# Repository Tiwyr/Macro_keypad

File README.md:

# Custom Macro Keypad

A custom-built programmable macro keypad featuring 12 mechanical keys, three rotary encoders, a dedicated layer button, and a color display.

The keypad is powered by an Adafruit KB2040 running CircuitPython and KMK firmware. It currently supports up to four configurable layers, allowing each key and encoder direction to perform a different action on every layer.

## Features

- 12 individually programmable mechanical keys
- Three programmable rotary encoders
- Dedicated layer-selection button
- Support for up to four configuration layers
- 320 × 240 color display
- Keyboard, media-key, macro, URL, application-launching, and MIDI actions
- Custom PCB
- Custom 3D-printable enclosure and keycaps
- Configurable display icons and layer names
- CircuitPython and KMK-based firmware

## Personal configuration

I currently use the three rotary encoders to control separate audio channels in SteelSeries GG Sonar. This is why the encoder logos on the chassit panel are what they are.

The encoder actions are programmable, and the encoder panel design can be modified using the included STEP or Fusion 360 files.

## Project structure

```text
Macro_keypad/
├── Board_Code/              CircuitPython and KMK firmware
├── Cad/                     Enclosure, keycap, and component models
├── Desktop_App/             Desktop configuration app in development
├── Macro_Keyboard_Circuit/  KiCad schematic and PCB files
└── images/                  README photographs and renders
```

## Firmware configuration

OBS! The config file is automatically configured using the desktop app.

Key and encoder actions are configured in:

```text
Board_Code/active_config.py
```

A basic key assignment looks like this:

```python
"KC.A"
```

Modifier combinations can be written directly:

```python
"KC.LCTRL(KC.C)"
"KC.LCTRL(KC.LSHIFT(KC.S))"
```

Other supported actions include:

```python
"KC.VOLU"
"KC.VOLD"
"URL:https://www.youtube.com/"
"LAUNCH:C:/Program Files/KiCad/10.0/bin/kicad.exe"
```

Each layer contains 12 key assignments. The three encoders have separate assignments for counterclockwise rotation, clockwise rotation, and their push-button action where applicable.

### Using the `MACRO:` wrapper

Use the `MACRO:` wrapper when one button should perform several actions, type text, include a delay, or behave differently when pressed, held, and released. Separate each part of a macro with `|`.

The supported macro commands are:

- `TEXT:` types text.
- `TAP:` presses and immediately releases a key or shortcut.
- `PRESS:` holds a key down.
- `RELEASE:` releases a held key.
- `DELAY:` waits for the specified number of milliseconds.

For example, this macro copies, waits 100 milliseconds, and then pastes:

```python
"MACRO:TAP:KC.LCTRL(KC.C)|DELAY:100|TAP:KC.LCTRL(KC.V)"
```

A key action without an explicit event prefix runs when the button is pressed i.e. `ON_PRESS:`. The optional event prefixes are:

- `ON_PRESS:` runs when the button is pressed.
- `ON_HOLD:` runs while the button is held.
- `ON_RELEASE:` runs when the button is released.

For example:

```python
"MACRO:ON_PRESS:TEXT:start|ON_HOLD:TAP:KC.A|ON_HOLD:DELAY:100|ON_RELEASE:TEXT:end"
```

Simple shortcuts do not require the macro wrapper and can be assigned directly, as shown above.

## Display icons

Icons are stored by layer and key number inside:

```text
Board_Code/images/
```

The desktop app has the feature to prepare images for the keypad display.

## CAD files

The `Cad` directory contains editable and printable files for the enclosure and keycaps, including:

- Fusion 360 files
- STEP models
- STL files
- 3MF print files
- Component reference models

The encoder logos can be edited to create a personalized panel.

## Desktop application

A PySide6 desktop application is currently in development.

The planned application will provide a graphical interface for:

- Editing key and encoder assignments
- Creating and managing profiles
- Changing layer names and display icons
- Sending configurations to the keypad
- Executing Windows-specific actions that cannot run directly on the board

At the moment, configuration is performed by editing `active_config.py` manually.

## Hardware

- Adafruit KB2040 with RP2040
- 12 mechanical keyboard switches
- Three rotary encoders
- ST7789-based 320 × 240 LCD
- Custom-designed PCB
- 3D-printed enclosure and keycaps

The gerber files for the PCB is found under `Macro_Keyboard_Cicuit`, for manufacturing I used [JLCPCB.com](https://jlcpcb.com/?from=VGEEEPCB1&utm_source=google&utm_medium=cpc&utm_campaign=23630608026&utm_content=803328468424&utm_term=p_pcb%20manufacturing&adgroupid=194779815580&utm_network=g_&gad_source=1&gad_campaignid=23630608026&gbraid=0AAAAApXmXsdJ7AZJWkuDSiIHlBB-qUlTP&gclid=CjwKCAjwvsvTBhBaEiwAmf-3njncny4jFNF5munrN3aUFo6y1D-hInMBf39UMtHOZ52Y8qgtHUBPVxoC710QAvD_BwE). Since the PCB is only two sided it is possible to manufacture by yourself if you have acess to the equipment. 

## Project status

This project is under active development. The keypad firmware, PCB, enclosure, display, keys, and encoders are functional. The desktop configuration application is still being developed.

## License

No license has been selected yet.

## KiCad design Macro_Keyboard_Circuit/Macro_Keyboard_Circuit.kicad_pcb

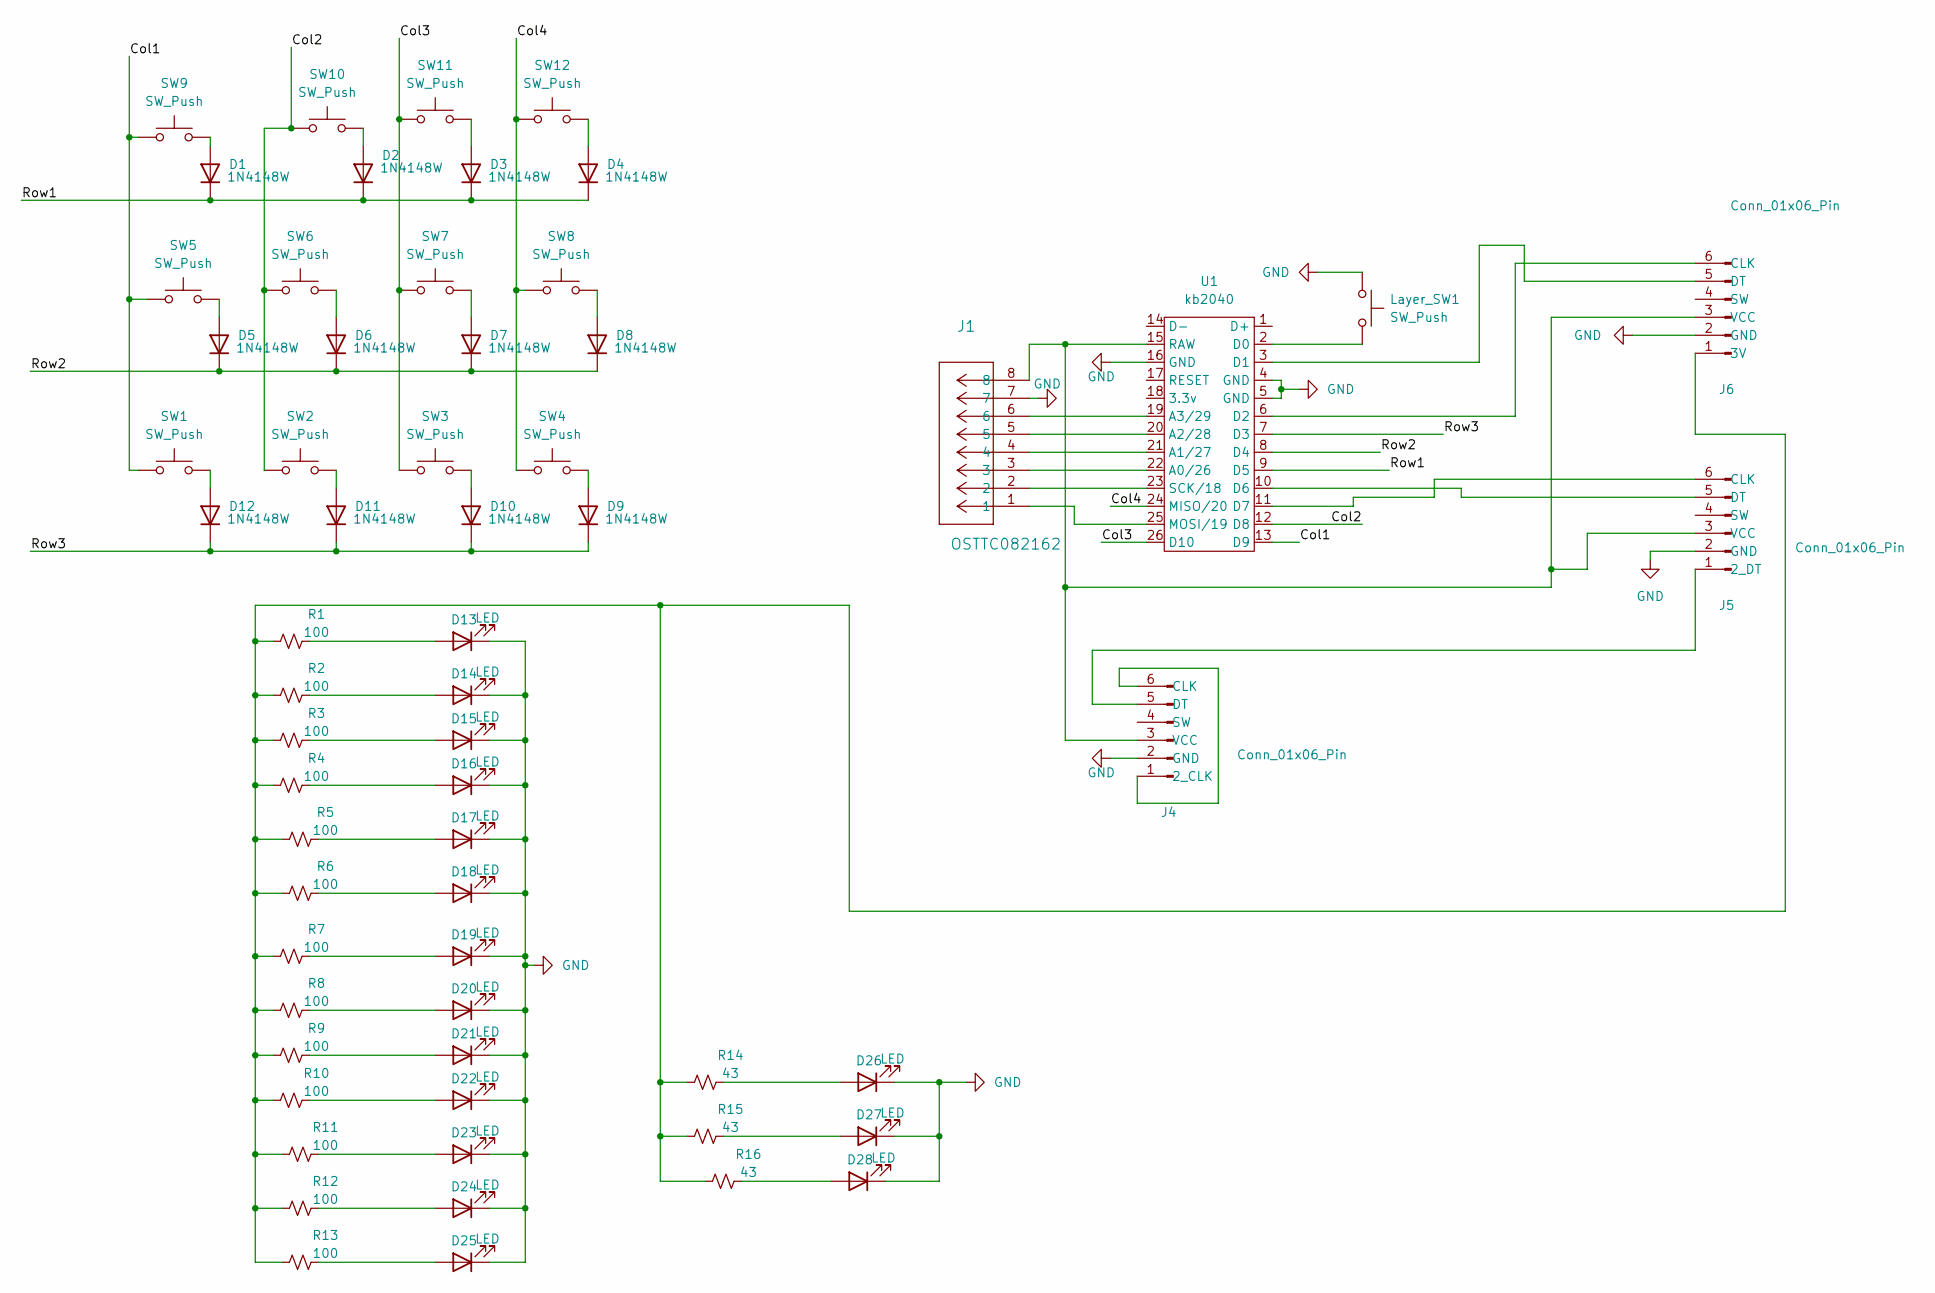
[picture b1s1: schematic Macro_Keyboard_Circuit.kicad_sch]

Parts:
D1, D2, D3, D4, D5, D6, D7, D8, D9, D10, D11, D12: 1N4148W; D_SOD-123
D13, D14, D15, D16, D17, D18, D19, D20, D21, D22, D23, D24, D25: LED; D_0603_1608Metric_Pad1.05x0.95mm_HandSolder_cherrymx_silk
D26, D27, D28: LED; D_A-405_P2.54mm_Vertical_AnodeUp
J1: OSTTC082162; CONN8_OSTTC082162_SHT
J4, J5, J6: Conn_01x06_Pin; PinHeader_1x06_P2.54mm_Vertical
Layer_SW1: SW_Push; SW_Cherry_modified
R1, R2, R3, R4, R5, R6, R7, R8, R9, R10, R11, R12, R13: 100; R_0603_1608Metric
R14, R15, R16: 43; R_0603_1608Metric
SW1, SW2, SW3, SW4, SW5, SW6, SW7, SW8, SW9, SW10, SW11, SW12: SW_Push; SW_Cherry_modified
U1: kb2040

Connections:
/Col1: SW1.1, SW5.1, SW9.1, U1.13 (D9)
/Col2: SW2.1, SW6.1, SW10.1, U1.12 (D8)
/Col3: SW3.1, SW7.1, SW11.1, U1.26 (D10)
/Col4: SW4.1, SW8.1, SW12.1, U1.24 (MISO/20)
/Row1: D1.1 (K), D2.1 (K), D3.1 (K), D4.1 (K), U1.9 (D5)
/Row2: D5.1 (K), D6.1 (K), D7.1 (K), D8.1 (K), U1.8 (D4)
/Row3: D9.1 (K), D10.1 (K), D11.1 (K), D12.1 (K), U1.7 (D3)
GND: D13.1 (K), D14.1 (K), D15.1 (K), D16.1 (K), D17.1 (K), D18.1 (K), D19.1 (K), D20.1 (K), D21.1 (K), D22.1 (K), D23.1 (K), D24.1 (K), D25.1 (K), D26.1 (K), D27.1 (K), D28.1 (K), J1.7, J4.2 (GND), J5.2 (GND), J6.2 (GND), Layer_SW1.1, U1.4 (GND), U1.5 (GND), U1.16 (GND)
unnamed: D1.2 (A), SW9.2
unnamed: D2.2 (A), SW10.2
unnamed: D3.2 (A), SW11.2
unnamed: D4.2 (A), SW12.2
unnamed: D5.2 (A), SW5.2
unnamed: D6.2 (A), SW6.2
unnamed: D7.2 (A), SW7.2
unnamed: D8.2 (A), SW8.2
unnamed: D9.2 (A), SW4.2
unnamed: D10.2 (A), SW3.2
unnamed: D11.2 (A), SW2.2
unnamed: D12.2 (A), SW1.2
unnamed: D13.2 (A), R1.2
unnamed: D14.2 (A), R2.2
unnamed: D15.2 (A), R3.2
unnamed: D16.2 (A), R4.2
unnamed: D17.2 (A), R5.2
unnamed: D18.2 (A), R6.2
unnamed: D19.2 (A), R7.2
unnamed: D20.2 (A), R8.2
unnamed: D21.2 (A), R9.2
unnamed: D22.2 (A), R10.2
unnamed: D23.2 (A), R11.2
unnamed: D24.2 (A), R12.2
unnamed: D25.2 (A), R13.2
unnamed: D26.2 (A), R14.2
unnamed: D27.2 (A), R15.2
unnamed: D28.2 (A), R16.2
unnamed: J4.1 (2_CLK), J4.6 (CLK)
unnamed: J4.5 (DT), J5.1 (2_DT)
unnamed: J1.8, J4.3 (VCC), J5.3 (VCC), J6.3 (VCC), U1.15 (RAW)
unnamed: J5.6 (CLK), U1.11 (D7)
unnamed: J5.5 (DT), U1.10 (D6)
unnamed: J6.1 (3V), R1.1, R2.1, R3.1, R4.1, R5.1, R6.1, R7.1, R8.1, R9.1, R10.1, R11.1, R12.1, R13.1, R14.1, R15.1, R16.1
unnamed: J6.6 (CLK), U1.6 (D2)
unnamed: J6.5 (DT), U1.3 (D1)
unnamed: J1.3, U1.22 (A0/26)
unnamed: J1.4, U1.21 (A1/27)
unnamed: J1.5, U1.20 (A2/28)
unnamed: J1.6, U1.19 (A3/29)
unnamed: Layer_SW1.2, U1.2 (D0)
unnamed: J1.1, U1.25 (MOSI/19)
unnamed: J1.2, U1.23 (SCK/18)

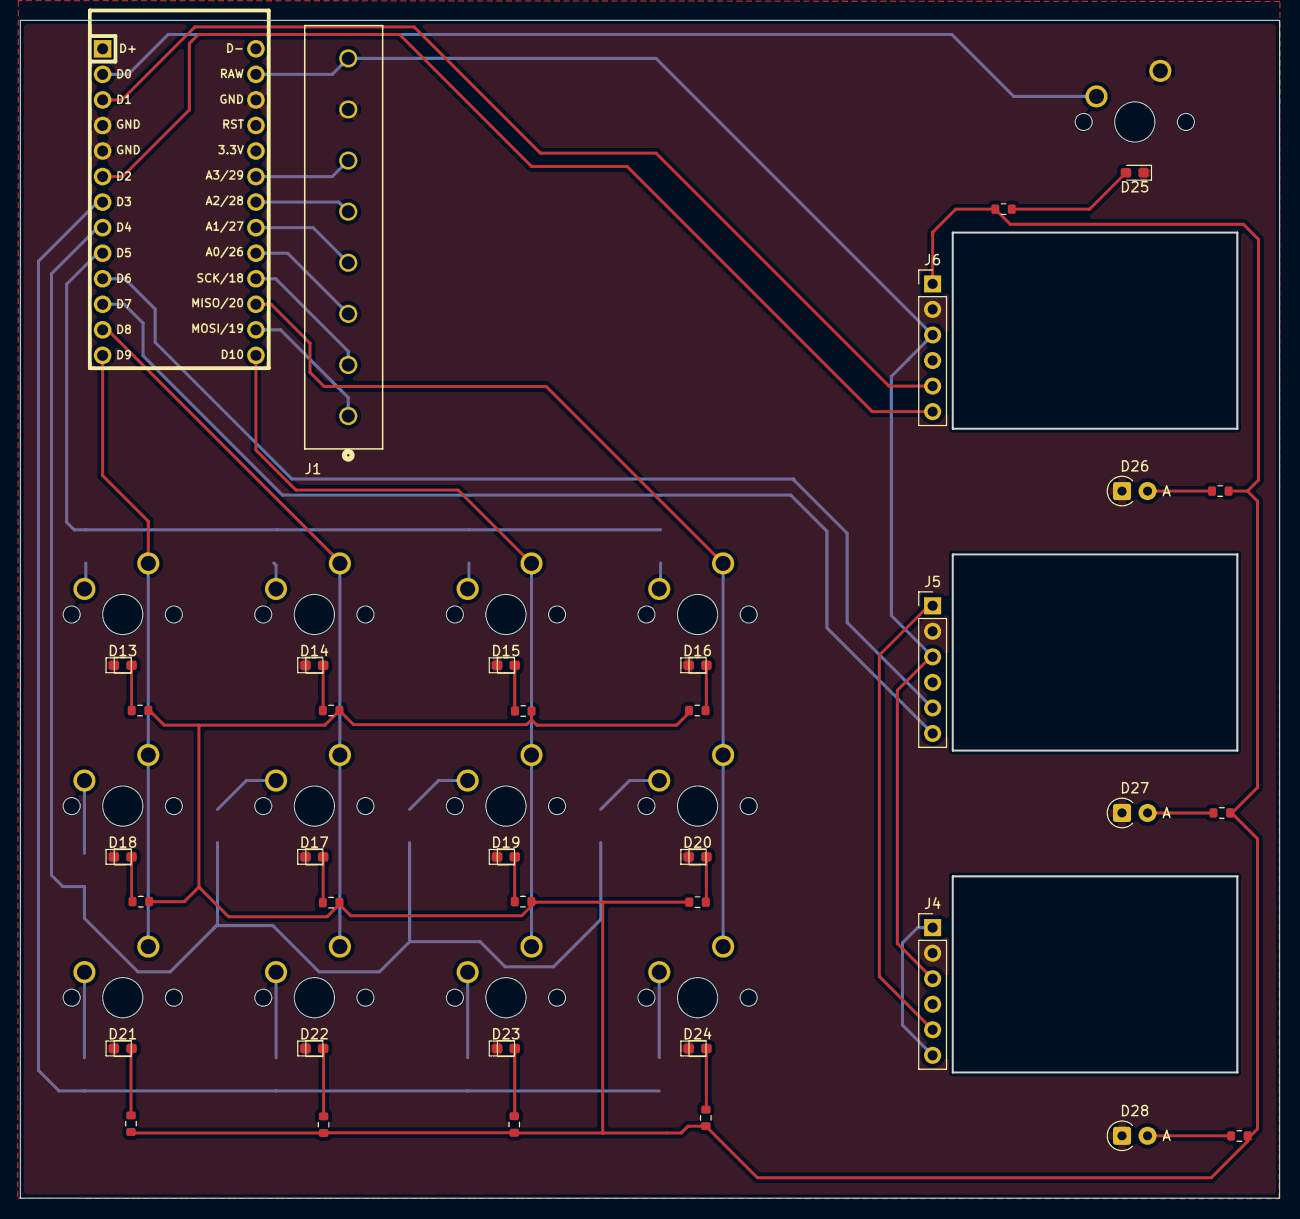
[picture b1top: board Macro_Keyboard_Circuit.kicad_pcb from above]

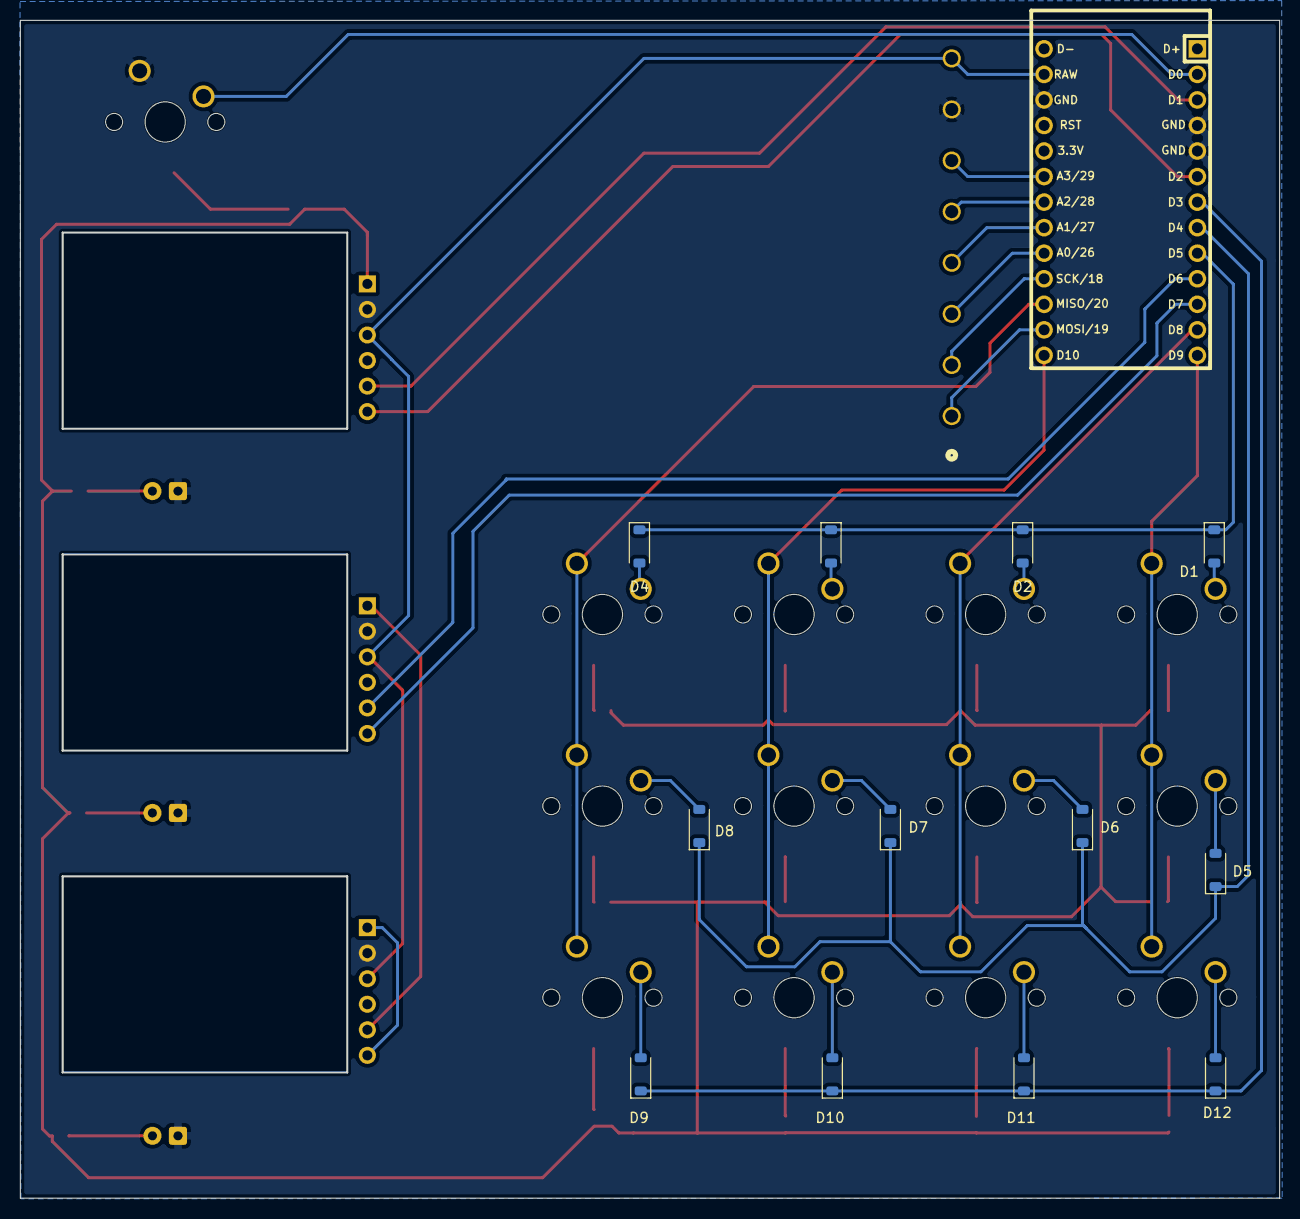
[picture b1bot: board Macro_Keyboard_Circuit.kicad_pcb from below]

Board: 2 copper layers, 125.1 x 117.0 mm, 62 parts (12 on the bottom side), 51 nets.

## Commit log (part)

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2025-11-29 almost complete kiCad-files, got a wroking code version with two encoders, two buttons and a working layer fuctionallity
2026-06-23 Restarting project with new structure
2026-06-23 Changed version of KMK and fixed missmatches with my added code. The macro function works now but could improve in function further.
